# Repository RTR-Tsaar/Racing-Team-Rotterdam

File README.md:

# Racing-Team-Rotterdam

## Overzicht

Deze repository bevat de software voor het drive-by-wire systeem, ontwikkeld voor de Racing Team Rotterdam Formula Student-auto. Het systeem is verdeeld over meerdere STM-microcontrollers, die elk verantwoordelijk zijn voor een specifieke subsystem. Samen zorgen ze voor precieze en betrouwbare controle van de stuur- en gaspedaalfunctionaliteit.

## Systeemcomponenten

Het drive-by-wire systeem is modulair opgebouwd, waarbij elke microcontroller een specifieke functie vervult:
1. **MCU**
	-	De MCU controleert alle subsystemen via CAN-bus. Het is de interface tussen de subsystemen en het toekomstige autonoom systeem.
	-	Is het brein van het complete systeem.
2.  **Steer-by-Wire**
    
    -   Verwerkt stuurinputs en bestuurt de elektronische stuuractuator.
    - Registreert huidige stuurhoek en geeft deze door aan de MCU.
3.  **Throttle-by-Wire**
    
    -   Registreert pedaalinputs en geeft deze door aan de MCU voor nauwkeurige motorbesturing.
4.  **Brake-by-wire**
    
    -   Registreert pedaalinputs en geeft deze door aan de MCU voor nauwkeurige motorbesturing.
5.  **Powertrain**
   
    -   Ontvangt gas en rem inputs van de MCU en stuurt hiermee de motorcontrollers aan.
    - Leest de CAN-bus berichten uit van de accu en geeft de belangrijkste door aan de MCU

## Inhoudsopgave

-   [Kenmerken](#kenmerken)
-   [Aan de slag](#aan-de-slag)
-   [Installatie](#installatie)
-   [Projectstructuur](#projectstructuur)
-   [Gebruik](#gebruik)
-   [Bijdragen](#bijdragen)
-   [Licentie](#licentie)
-   [Contact](#contact)

## Kenmerken

-   Modulair drive-by-wire systeem met gescheiden microcontrollers.
-   CAN bus communicatie voor naadloze integratie van subsystemen.
-   Hoge responsiviteit voor nauwkeurige controle in Formula Student-races.

## Aan de slag

Om het systeem lokaal op te zetten en te testen, volg je deze stappen:

### Via Github Desktop

1.  **Repository klonen**
    
    -   Open GitHub Desktop.
    -   Klik op **File** > **Clone Repository**.
    -   Ga naar het tabblad **URL** en voer de volgende link in:
        
        ```
        https://github.com/RTR-Tsaar/Racing-Team-Rotterdam.git
        
        ```
        
    -   Kies een lokale map waar je de repository wilt opslaan en klik op **Clone**.
2.  **Project openen**
    
    -   Navigeer naar de lokaal gekloonde map via Verkenner (Windows) of Finder (Mac).
    -   Open de map van het subsystem waaraan je wilt werken, bijvoorbeeld `steer-by-wire/`.
3.  **STM32CubeIDE installeren**
    
    -   Als je dat nog niet hebt gedaan, installeer [STM32CubeIDE](https://www.st.com/en/development-tools/stm32cubeide.html).
    -   Open de folder van het gekozen subsystem in STM32CubeIDE.

### Via Terminal
1.  Clone deze repository:
    
    ```bash
    git clone https://github.com/RTR-Tsaar/Racing-Team-Rotterdam.git
    cd Racing-Team-Rotterdam
    
    ```
    
2.  Installeer [STM32CubeIDE](https://www.st.com/en/development-tools/stm32cubeide.html) of een andere ontwikkelomgeving voor STM-microcontrollers.
    
3.  Open de map van het subsystem dat je wilt gebruiken.

## Installatie

Elk subsystem bevindt zich in een aparte map:

-   `steer-by-wire/`
-   `throttle-by-wire/`
-   `brake-by-wire/`
-   `aandrijving/`
-   `mcu/`
-   `CAN_bus_algemeen` (CAN-bus poc en testomgeving)

Volg de instructies in de README-bestanden van de respectieve mappen om de software te bouwen en te uploaden naar de bijbehorende microcontroller. Hier vind je ook meer uitleg over de werking van de code.

## Projectstructuur

```
Racing-Team-Rotterdam/
├── CAN_bus_algemeen/ (CAN-bus poc en testomgeving)
├── steer-by-wire/  
├── throttle-by-wire/  
├── brake-by-wire/
├── aandrijving/
├── mcu/  
└── docs/ (bevat systeemarchitectuur en ontwerpdocumentatie)  

```

## Gebruik

1. Verbind de microcontrollers volgens het aansluitschema in de `README.md` van het project dat u wilt gebruiken. 
2. Flash de software naar de bijbehorende STM-microcontroller met behulp van STM32CubeIDE en een ST-Link programmer.

## Bijdragen

Bijdragen zijn van harte welkom! Volg deze stappen om bij te dragen:

1.  Fork deze repository.
2.  Maak een nieuwe branch aan voor je wijzigingen.
3.  Commit je wijzigingen en push ze naar je fork.
4.  Open een pull request en beschrijf je wijzigingen.

## Licentie

Dit project is gelicenseerd onder de MIT-licentie. Zie het LICENSE-bestand voor meer informatie.

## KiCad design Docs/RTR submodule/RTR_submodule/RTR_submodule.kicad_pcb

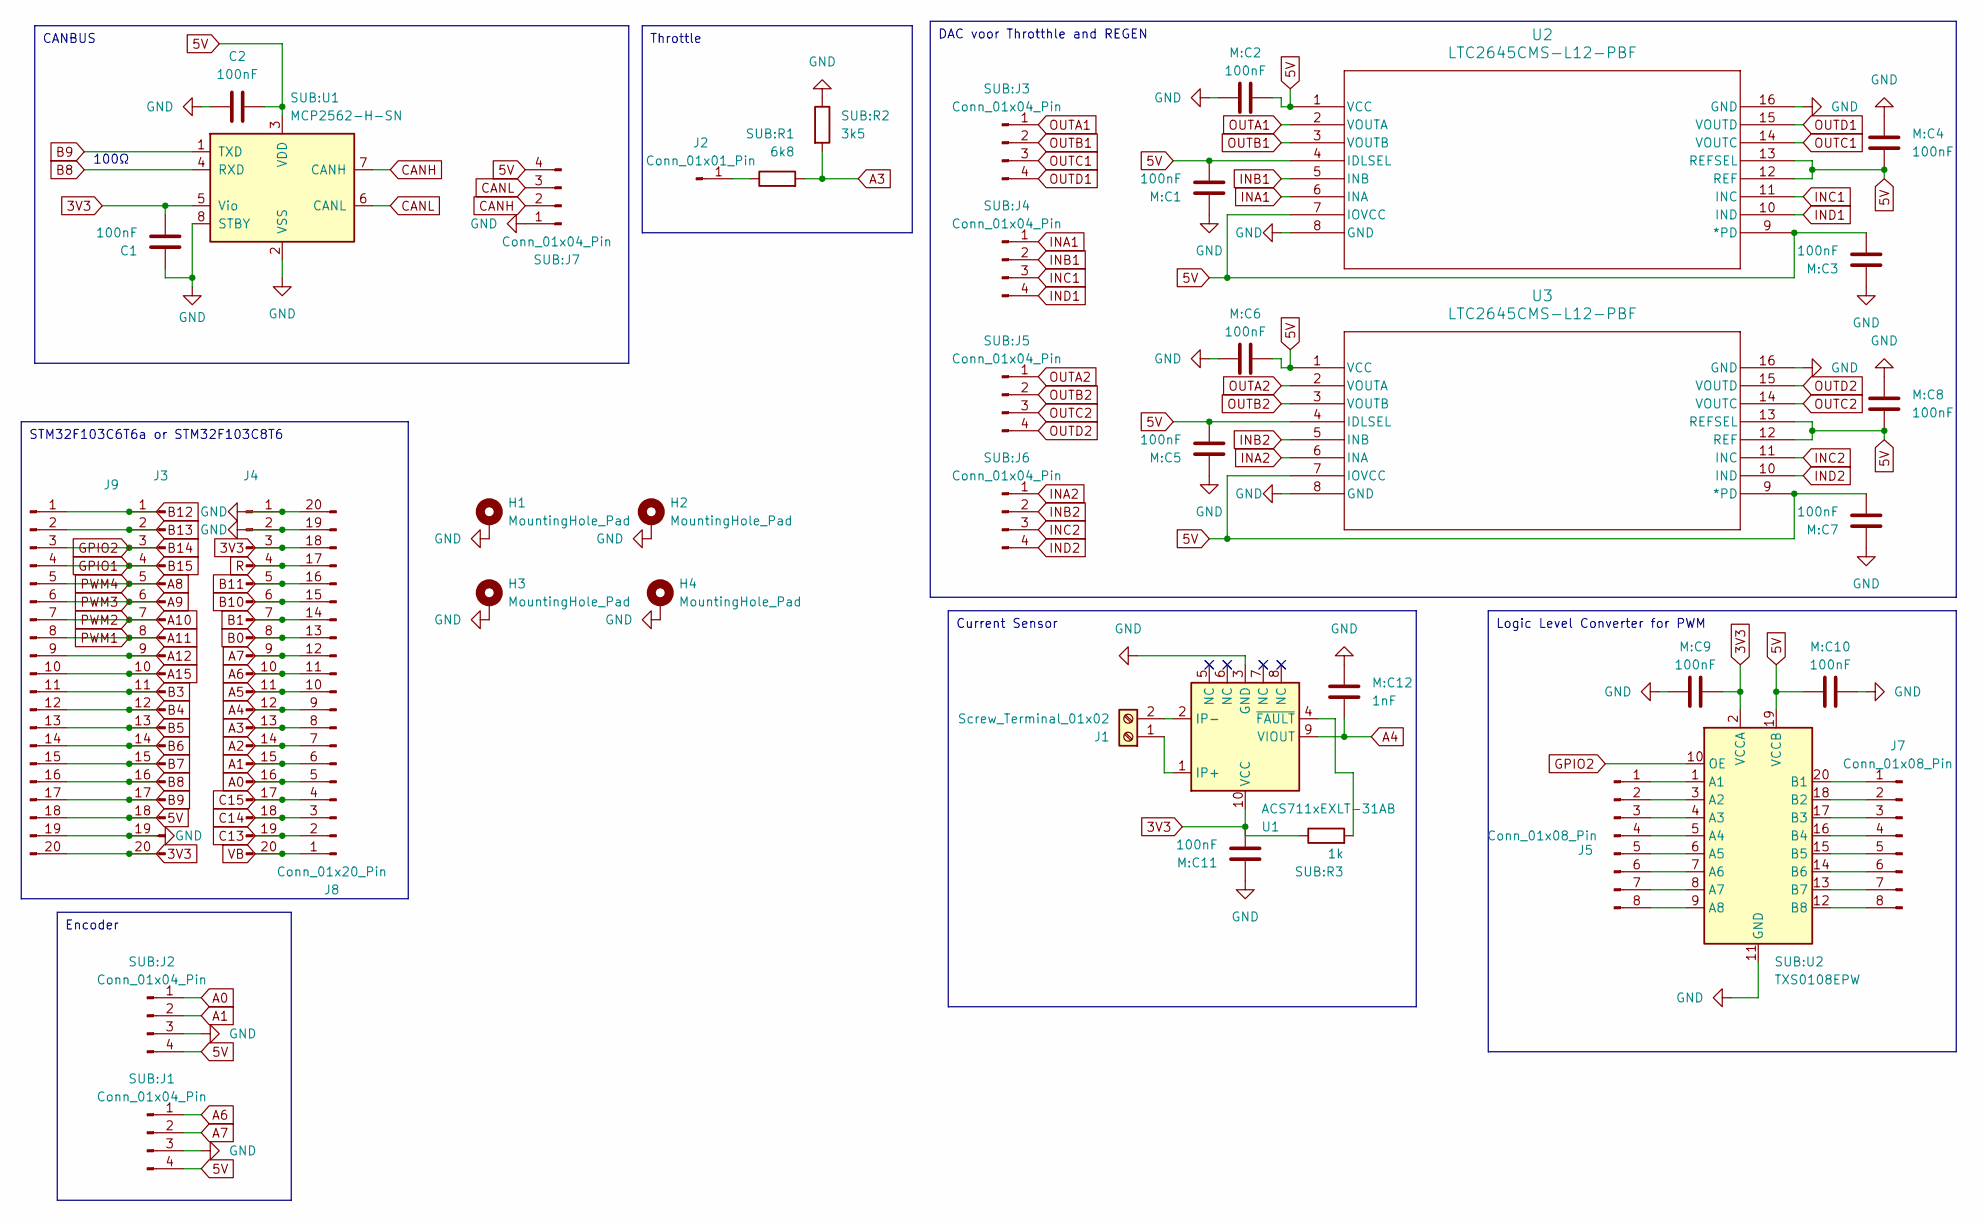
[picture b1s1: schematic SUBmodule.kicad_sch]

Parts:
C1, C2: 100nF; C_0603_1608Metric_Pad1.08x0.95mm_HandSolder
H1, H2, H3, H4: MountingHole_Pad; MountingHole_2.2mm_M2_Pad
J1: Screw_Terminal_01x02; PinSocket_1x02_P2.54mm_Vertical
J2: Conn_01x01_Pin; PinHeader_1x01_P2.54mm_Vertical
J3, J4, J8, J9: Conn_01x20_Pin; PinHeader_1x20_P2.54mm_Vertical
J5, J7: Conn_01x08_Pin; PinHeader_1x08_P2.54mm_Vertical
M:C1, M:C2, M:C3, M:C4, M:C5, M:C6, M:C7, M:C8, M:C9, M:C10, M:C11: 100nF; C_0603_1608Metric_Pad1.08x0.95mm_HandSolder
M:C12: 1nF; C_0603_1608Metric_Pad1.08x0.95mm_HandSolder
SUB:J1, SUB:J2, SUB:J3, SUB:J4, SUB:J5, SUB:J6, SUB:J7: Conn_01x04_Pin; PinHeader_1x04_P2.54mm_Vertical
SUB:R1: 6k8; R_Axial_DIN0204_L3.6mm_D1.6mm_P7.62mm_Horizontal
SUB:R2: 3k5; R_Axial_DIN0204_L3.6mm_D1.6mm_P7.62mm_Horizontal
SUB:R3: 1k; R_Axial_DIN0204_L3.6mm_D1.6mm_P7.62mm_Horizontal
SUB:U1: MCP2562-H-SN; SOIC-8_3.9x4.9mm_P1.27mm
SUB:U2: TXS0108EPW; TSSOP-20_4.4x6.5mm_P0.65mm
U1: ACS711xEXLT-31AB; Allegro_QFN-12-10-1EP_3x3mm_P0.5mm
U2, U3: LTC2645CMS-L12-PBF; SOP50P490X110-16N

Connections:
3V3: C1.2, J3.20, J4.3, J8.18, J9.20, M:C9.1, M:C11.1, SUB:R3.1, SUB:U1.5 (Vio), SUB:U2.2 (VCCA), U1.10 (VCC)
5V: C2.2, J3.18, J9.18, M:C1.1, M:C2.1, M:C3.1, M:C4.1, M:C5.1, M:C6.1, M:C7.1, M:C8.1, M:C10.1, SUB:J1.4, SUB:J2.4, SUB:J7.4, SUB:U1.3 (VDD), SUB:U2.19 (VCCB), U2.1 (VCC), U2.4 (IDLSEL), U2.7 (IOVCC), U2.9 (*PD), U2.12 (REF), U2.13 (REFSEL), U3.1 (VCC), U3.4 (IDLSEL), U3.7 (IOVCC), U3.9 (*PD), U3.12 (REF), U3.13 (REFSEL)
A0: J4.16, J8.5, SUB:J2.1
A1: J4.15, J8.6, SUB:J2.2
A2: J4.14, J8.7
A3: J4.13, J8.8, SUB:R1.2, SUB:R2.2
A4: J4.12, J8.9, M:C12.1, U1.9 (VIOUT)
A5: J4.11, J8.10
A6: J4.10, J8.11, SUB:J1.1
A7: J4.9, J8.12, SUB:J1.2
A8: J3.5, J9.5
A9: J3.6, J9.6
A10: J3.7, J9.7
A11: J3.8, J9.8
A12: J3.9, J9.9
A15: J3.10, J9.10
B0: J4.8, J8.13
B1: J4.7, J8.14
B3: J3.11, J9.11
B4: J3.12, J9.12
B5: J3.13, J9.13
B6: J3.14, J9.14
B7: J3.15, J9.15
B8: J3.16, J9.16, SUB:U1.4 (RXD)
B9: J3.17, J9.17, SUB:U1.1 (TXD)
B10: J4.6, J8.15
B11: J4.5, J8.16
B12: J3.1, J9.1
B13: J3.2, J9.2
B14: J3.3, J9.3, SUB:U2.10 (OE)
B15: J3.4, J9.4
C13: J4.19, J8.2
C14: J4.18, J8.3
C15: J4.17, J8.4
CANH: SUB:J7.2, SUB:U1.7 (CANH)
CANL: SUB:J7.3, SUB:U1.6 (CANL)
GND: C1.1, C2.1, H1.1, H2.1, H3.1, H4.1, J3.19, J4.1, J4.2, J8.19, J8.20, J9.19, M:C1.2, M:C2.2, M:C3.2, M:C4.2, M:C5.2, M:C6.2, M:C7.2, M:C8.2, M:C9.2, M:C10.2, M:C11.2, M:C12.2, SUB:J1.3, SUB:J2.3, SUB:J7.1, SUB:R2.1, SUB:U1.2 (VSS), SUB:U1.8 (STBY), SUB:U2.11 (GND), U1.3 (GND), U2.8 (GND), U2.16 (GND), U3.8 (GND), U3.16 (GND)
INA1: SUB:J4.1, U2.6 (INA)
INA2: SUB:J6.1, U3.6 (INA)
INB1: SUB:J4.2, U2.5 (INB)
INB2: SUB:J6.2, U3.5 (INB)
INC1: SUB:J4.3, U2.11 (INC)
INC2: SUB:J6.3, U3.11 (INC)
IND1: SUB:J4.4, U2.10 (IND)
IND2: SUB:J6.4, U3.10 (IND)
unnamed: J1.1, U1.1 (IP+)
unnamed: J1.2, U1.2 (IP-)
unnamed: J2.1, SUB:R1.1
unnamed: J5.1, SUB:U2.1 (A1)
unnamed: J5.2, SUB:U2.3 (A2)
unnamed: J5.3, SUB:U2.4 (A3)
unnamed: J5.4, SUB:U2.5 (A4)
unnamed: J5.5, SUB:U2.6 (A5)
unnamed: J5.6, SUB:U2.7 (A6)
unnamed: J5.7, SUB:U2.8 (A7)
unnamed: J5.8, SUB:U2.9 (A8)
unnamed: J7.1, SUB:U2.20 (B1)
unnamed: J7.2, SUB:U2.18 (B2)
unnamed: J7.3, SUB:U2.17 (B3)
unnamed: J7.4, SUB:U2.16 (B4)
unnamed: J7.5, SUB:U2.15 (B5)
unnamed: J7.6, SUB:U2.14 (B6)
unnamed: J7.7, SUB:U2.13 (B7)
unnamed: J7.8, SUB:U2.12 (B8)
unnamed: SUB:R3.2, U1.4 (~FAULT)
OUTA1: SUB:J3.1, U2.2 (VOUTA)
OUTA2: SUB:J5.1, U3.2 (VOUTA)
OUTB1: SUB:J3.2, U2.3 (VOUTB)
OUTB2: SUB:J5.2, U3.3 (VOUTB)
OUTC1: SUB:J3.3, U2.14 (VOUTC)
OUTC2: SUB:J5.3, U3.14 (VOUTC)
OUTD1: SUB:J3.4, U2.15 (VOUTD)
OUTD2: SUB:J5.4, U3.15 (VOUTD)
R: J4.4, J8.17
VB: J4.20, J8.1

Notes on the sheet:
Encoder
DAC voor Throtthle and REGEN
Current Sensor
CANBUS
STM32F103C6T6a or STM32F103C8T6
Throttle
Logic Level Converter for PWM
100Ω

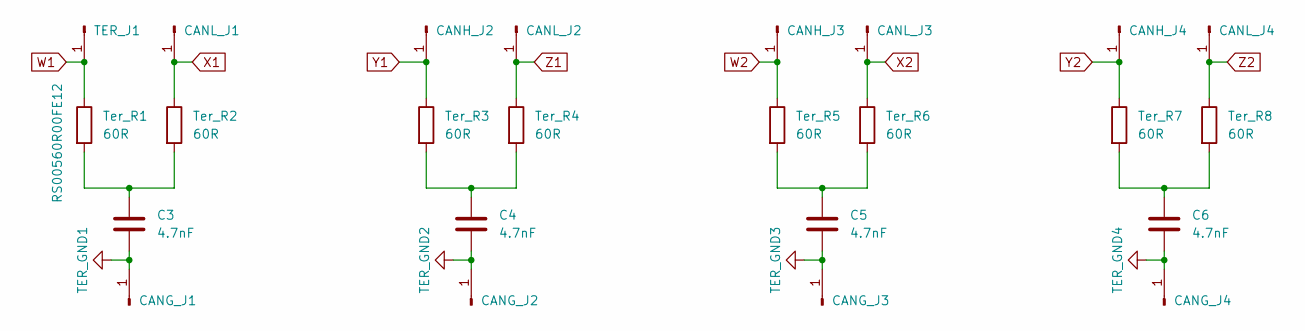
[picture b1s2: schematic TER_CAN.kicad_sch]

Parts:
C3, C4, C5, C6: 4.7nF; C_0603_1608Metric_Pad1.08x0.95mm_HandSolder
CANG_J1, CANG_J2, CANG_J3, CANG_J4: Conn_01x01_Pin; PinSocket_1x01_P2.54mm_Vertical
CANH_J2, CANH_J3, CANH_J4: Conn_01x01_Pin; PinSocket_1x01_P2.54mm_Vertical
CANL_J1, CANL_J2, CANL_J3, CANL_J4: Conn_01x01_Pin; PinSocket_1x01_P2.54mm_Vertical
TER_J1: Conn_01x01_Pin; PinSocket_1x01_P2.54mm_Vertical
Ter_R1, Ter_R2, Ter_R3, Ter_R4, Ter_R5, Ter_R6, Ter_R7, Ter_R8: 60R; R_Axial_DIN0204_L3.6mm_D1.6mm_P7.62mm_Horizontal

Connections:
unnamed: C3.1, Ter_R1.2, Ter_R2.2
unnamed: C4.1, Ter_R3.2, Ter_R4.2
unnamed: C5.1, Ter_R5.2, Ter_R6.2
unnamed: C6.1, Ter_R7.2, Ter_R8.2
TER_GND1: C3.2, CANG_J1.1
TER_GND2: C4.2, CANG_J2.1
TER_GND3: C5.2, CANG_J3.1
TER_GND4: C6.2, CANG_J4.1
W1: Ter_R1.1; also elsewhere on the board
W2: CANH_J3.1, Ter_R5.1
X1: CANL_J1.1, Ter_R2.1
X2: CANL_J3.1, Ter_R6.1
Y1: CANH_J2.1, Ter_R3.1
Y2: CANH_J4.1, Ter_R7.1
Z1: CANL_J2.1, Ter_R4.1
Z2: CANL_J4.1, Ter_R8.1

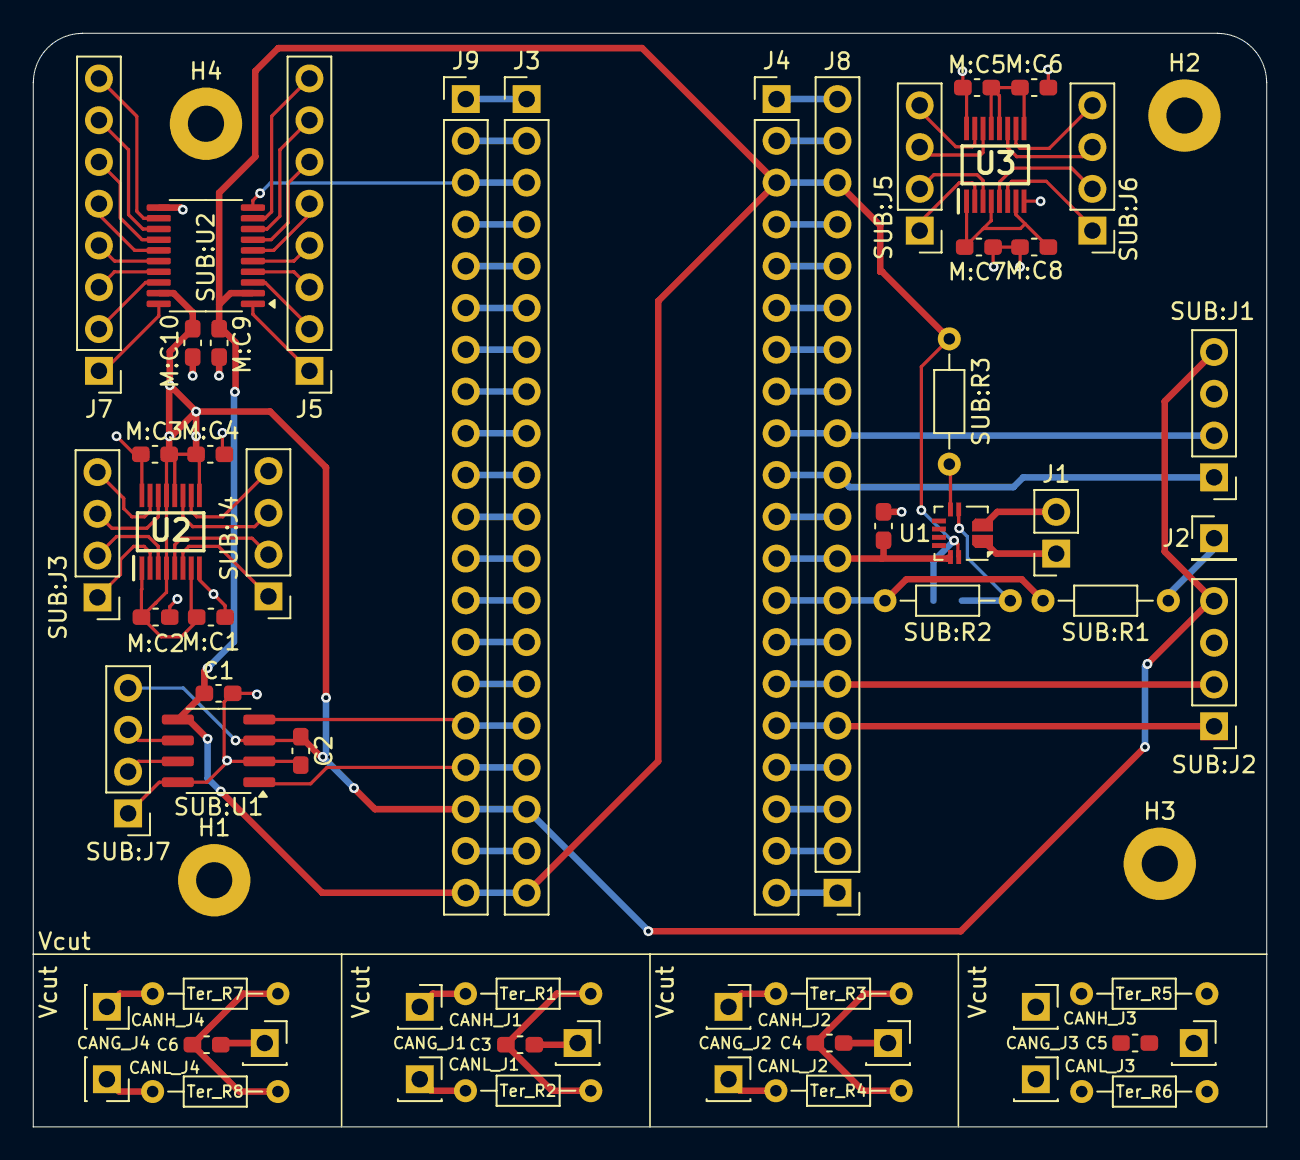
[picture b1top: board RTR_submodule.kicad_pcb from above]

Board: 2 copper layers, 75.0 x 66.5 mm, 65 parts (1 on the bottom side), 91 nets.

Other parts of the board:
CANH_J1: Conn_01x01_Pin; PinSocket_1x01_P2.54mm_Vertical

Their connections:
W1: CANH_J1.1; also elsewhere on the board

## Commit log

2024-11-12 Generated code from .ioc for ThrottleByWire
2024-11-13 rebuild project on .ioc file for stm32f103c8t6
2024-11-13 fixed clock config
2024-11-14 rebuilt project for both c8t6 and c6t6a variants
2024-11-14 UPloaden van alles CANBUSS
2024-11-14 Updated .ioc file to complete pinout
2024-11-15 started work on steer by wire
2024-11-17 added motorControl
    motorControl gradually speeds up the motor when beginning the steering process, and gradually slows down when reaching the desired angle. This is done to protect the 24v dc motor
2024-11-18 improved motorControl
2024-11-18 made PWM cycle stable after ramp up
2024-11-19 changed SBW code to now implement a PID
2024-11-20 CAN ding idk
2024-11-20 Data handler
2024-11-21 minor update on PID and created encoder.cpp
2024-11-26 improved PID by adding constraints(WIP)
2024-12-01 improved readability and consistency
2024-12-01 reworked timer settings
2024-12-02 wrote code to read out encoders
2024-12-03 built a testproject for in vscode
2024-12-04 rebuilt vscode test and fixed cmake file
2024-12-16 minor fixes and tested encoder reading
2024-12-17 worked on canbus communication
2024-12-18 built new stbw project because of can issues
2024-12-18 configured SBWv2
2024-12-18 added encoder and motorcontrol to SBWv2
2024-12-18 added a data splitter to CANBus
2024-12-19 added datasplitter and merger for canbus frames
2024-12-19 started work on CanID recognition
2024-12-20 started on encoder calibration
2025-01-05 added encoder calibration
2025-01-05 changed project config to add analog input
2025-01-05 current sensor code written
2025-01-07 implemented calibration to SbW
2025-01-07 bugfixing encoder calibration
2025-01-08 completed calibration and angle reading code
2025-01-08 cleaned up TbW
2025-01-09 rebuilt SbW project
2025-01-09 fixed timer issue
    fixed issue where encoder and motor where on same timer, causing the count of the encoder to increase motor speed
2025-01-12 added (incomplete) canbus tbw
2025-01-15 fixed hard_fault issue in encoderCalibration
2025-01-16 fixed PID int overflow issue
2025-01-16 removed unused stm projects
2025-01-19 fixed debugger issue
2025-01-22 minor change
2025-01-22 Create LICENSE
2025-01-28 added comments to SbW
2025-01-28 Toevoegen van code aandrijving
2025-02-03 cleaned up repo
2025-02-03 added comments for clarity
2025-02-04 updated CANbus communication
    updated the canbus communication of the steer- and throttle by wire systems to prepare them for integration with the MCU.
2025-02-05 added readme for throttle by wire
2025-02-05 added readme for steer by wire
2025-02-05 added documentation
2025-02-05 updated readme's
2025-02-05 added hardware documentation
2025-02-06 set CAN-bus mode to normal
2025-02-10 Add files via upload
    Laaste files voor overdracht succes volgende team hoop dat het gaat lukken. :)
